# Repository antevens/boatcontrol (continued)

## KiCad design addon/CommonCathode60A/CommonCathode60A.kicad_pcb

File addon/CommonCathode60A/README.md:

Addon board for Boatcontrol 32.

The Boatcontrol 32 is a smart distribution panel and electrical system for on/off-grid and hybrid backup power systems that need to handle 12-24v DC 110-115v AC and 200-250V AC systems.
A perfect companion to a SMA Sunny Island or Sunny Boy Storage, Fronius or other battery inverters.

It's a one stop PCB that allows a Raspberry Pi (RPi) or Nvidia Jetson to control your entire electrical system while retaining full analog control from external switches and allowing manual override onboard in case of emergencies.
This addon board adds 8 x 60 AC/DC relays.
https://github.com/antevens/boatcontrol/tree/master/addon/CommonCathode60A

BoatControl
https://github.com/antevens/boatcontrol

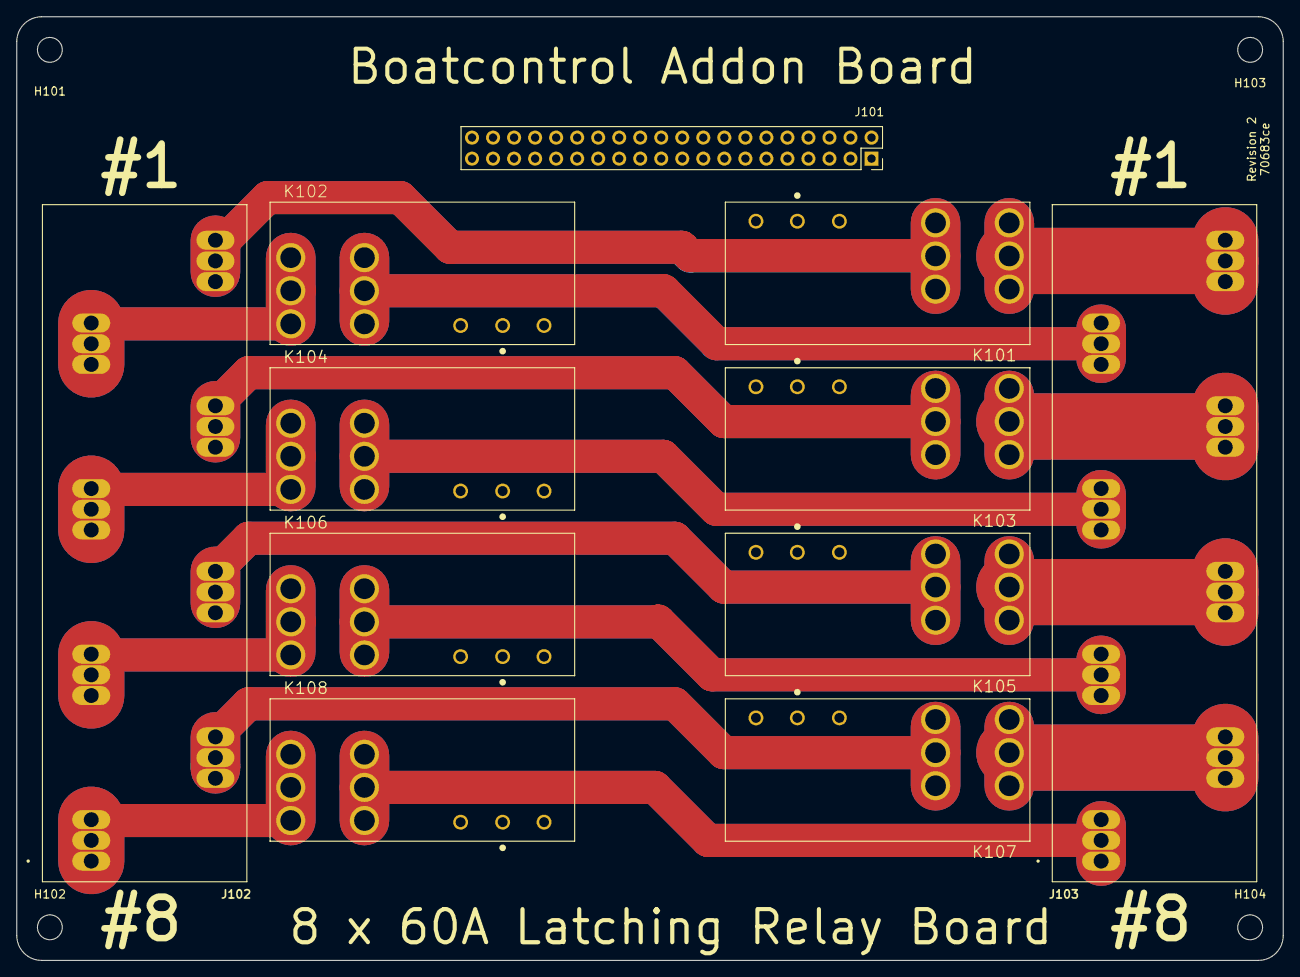
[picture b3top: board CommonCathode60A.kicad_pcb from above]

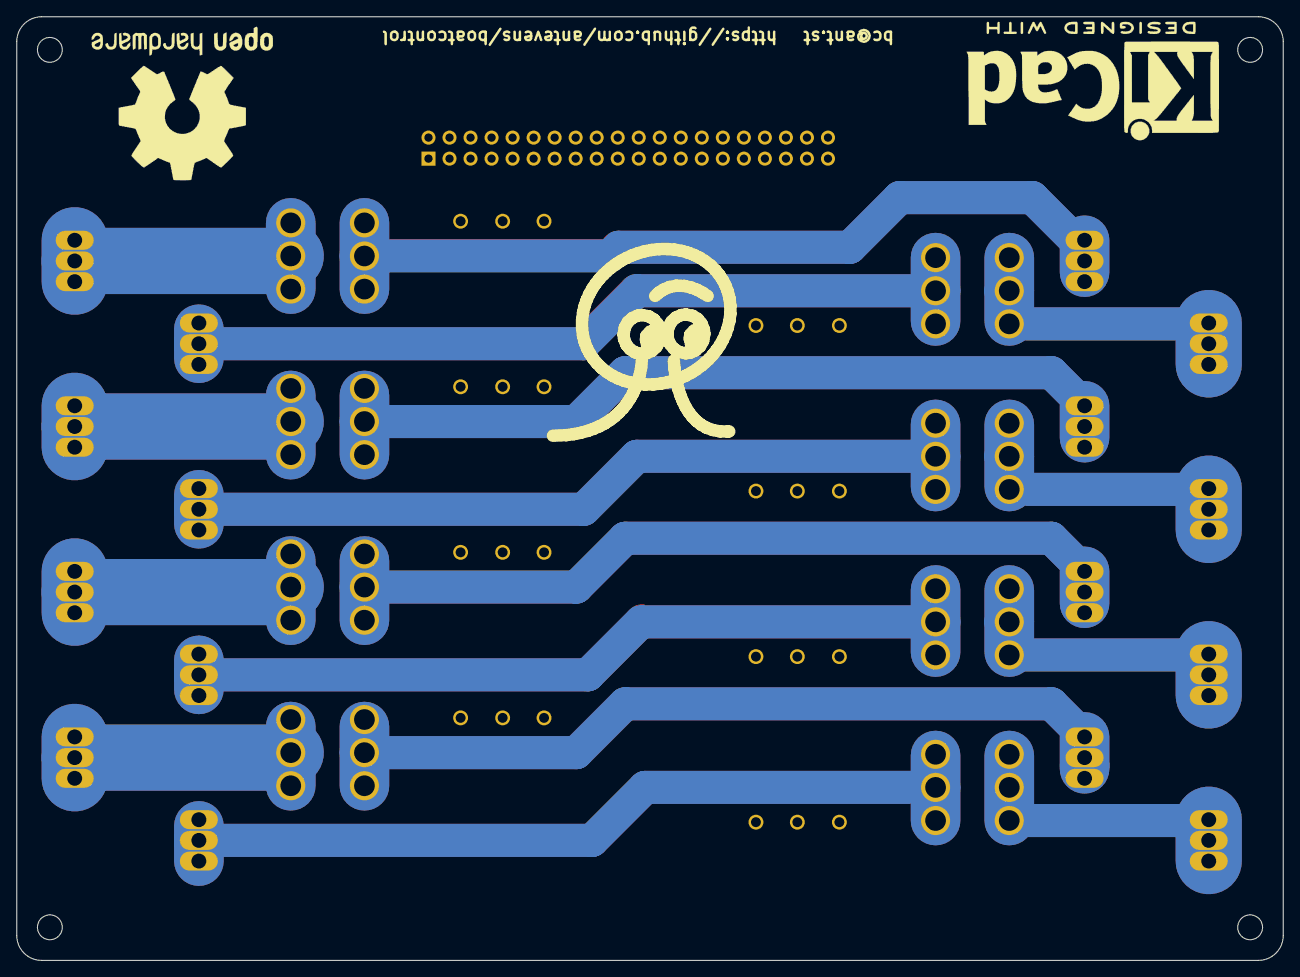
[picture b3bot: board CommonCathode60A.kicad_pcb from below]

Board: 4 copper layers, 153.0 x 114.0 mm, 18 parts (3 on the bottom side), 33 nets.

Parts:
G102: LOGO_ANT; Ant_Logo_SilkScreen
H101, H102, H103, H104: MountingHole; MountingHole_3mm
J101: Conn_02x20_Odd_Even Header; PinSocket_2x20_P2.54mm_Vertical
J102, J103: TBL008V-1000-08BE; CUI_TBL008V-1000-08BE
K101, K102, K103, K104, K105, K106, K107, K108: EW60-1A3-CL12D04; TE_2071366-2
LOGO101: Logo_Open_Hardware_Large; KiCad-Logo2_12mm_SilkScreen
LOGO102: Logo_Open_Hardware_Large; OSHW-Logo2_24.3x20mm_SilkScreen

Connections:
/K1_COIL_OFF: J101.3, J101.4, K101.A2
/K1_COIL_ON: J101.1, J101.2, K101.A3
/K1_IN: J102.8_1, J102.8_2, J102.8_3, K101.4, K101.5, K101.6
/K1_OUT: J103.8_1, J103.8_2, J103.8_3, K101.1, K101.2, K101.3
/K2_COIL_OFF: J101.7, J101.8, K102.A3
/K2_COIL_ON: J101.5, J101.6, K102.A2
/K2_IN: J102.7_1, J102.7_2, J102.7_3, K102.1, K102.2, K102.3
/K2_OUT: J103.7_1, J103.7_2, J103.7_3, K102.4, K102.5, K102.6
/K3_COIL_OFF: J101.11, J101.12, K103.A2
/K3_COIL_ON: J101.9, J101.10, K103.A3
/K3_IN: J102.6_1, J102.6_2, J102.6_3, K103.4, K103.5, K103.6
/K3_OUT: J103.6_1, J103.6_2, J103.6_3, K103.1, K103.2, K103.3
/K4_COIL_OFF: J101.15, J101.16, K104.A3
/K4_COIL_ON: J101.13, J101.14, K104.A2
/K4_IN: J102.5_1, J102.5_2, J102.5_3, K104.1, K104.2, K104.3
/K4_OUT: J103.5_1, J103.5_2, J103.5_3, K104.4, K104.5, K104.6
/K5_COIL_OFF: J101.19, J101.20, K105.A2
/K5_COIL_ON: J101.17, J101.18, K105.A3
/K5_IN: J102.4_1, J102.4_2, J102.4_3, K105.4, K105.5, K105.6
/K5_OUT: J103.4_1, J103.4_2, J103.4_3, K105.1, K105.2, K105.3
/K6_COIL_OFF: J101.23, J101.24, K106.A3
/K6_COIL_ON: J101.21, J101.22, K106.A2
/K6_IN: J102.3_1, J102.3_2, J102.3_3, K106.1, K106.2, K106.3
/K6_OUT: J103.3_1, J103.3_2, J103.3_3, K106.4, K106.5, K106.6
/K7_COIL_OFF: J101.27, J101.28, K107.A2
/K7_COIL_ON: J101.25, J101.26, K107.A3
/K7_IN: J102.2_1, J102.2_2, J102.2_3, K107.4, K107.5, K107.6
/K7_OUT: J103.2_1, J103.2_2, J103.2_3, K107.1, K107.2, K107.3
/K8_COIL_OFF: J101.31, J101.32, K108.A3
/K8_COIL_ON: J101.29, J101.30, K108.A2
/K8_IN: J102.1_1, J102.1_2, J102.1_3, K108.1, K108.2, K108.3
/K8_OUT: J103.1_1, J103.1_2, J103.1_3, K108.4, K108.5, K108.6
GND: J101.33, J101.34, J101.35, J101.36, J101.37, J101.38, J101.39, J101.40, K101.A1, K102.A1, K103.A1, K104.A1, K105.A1, K106.A1, K107.A1, K108.A1

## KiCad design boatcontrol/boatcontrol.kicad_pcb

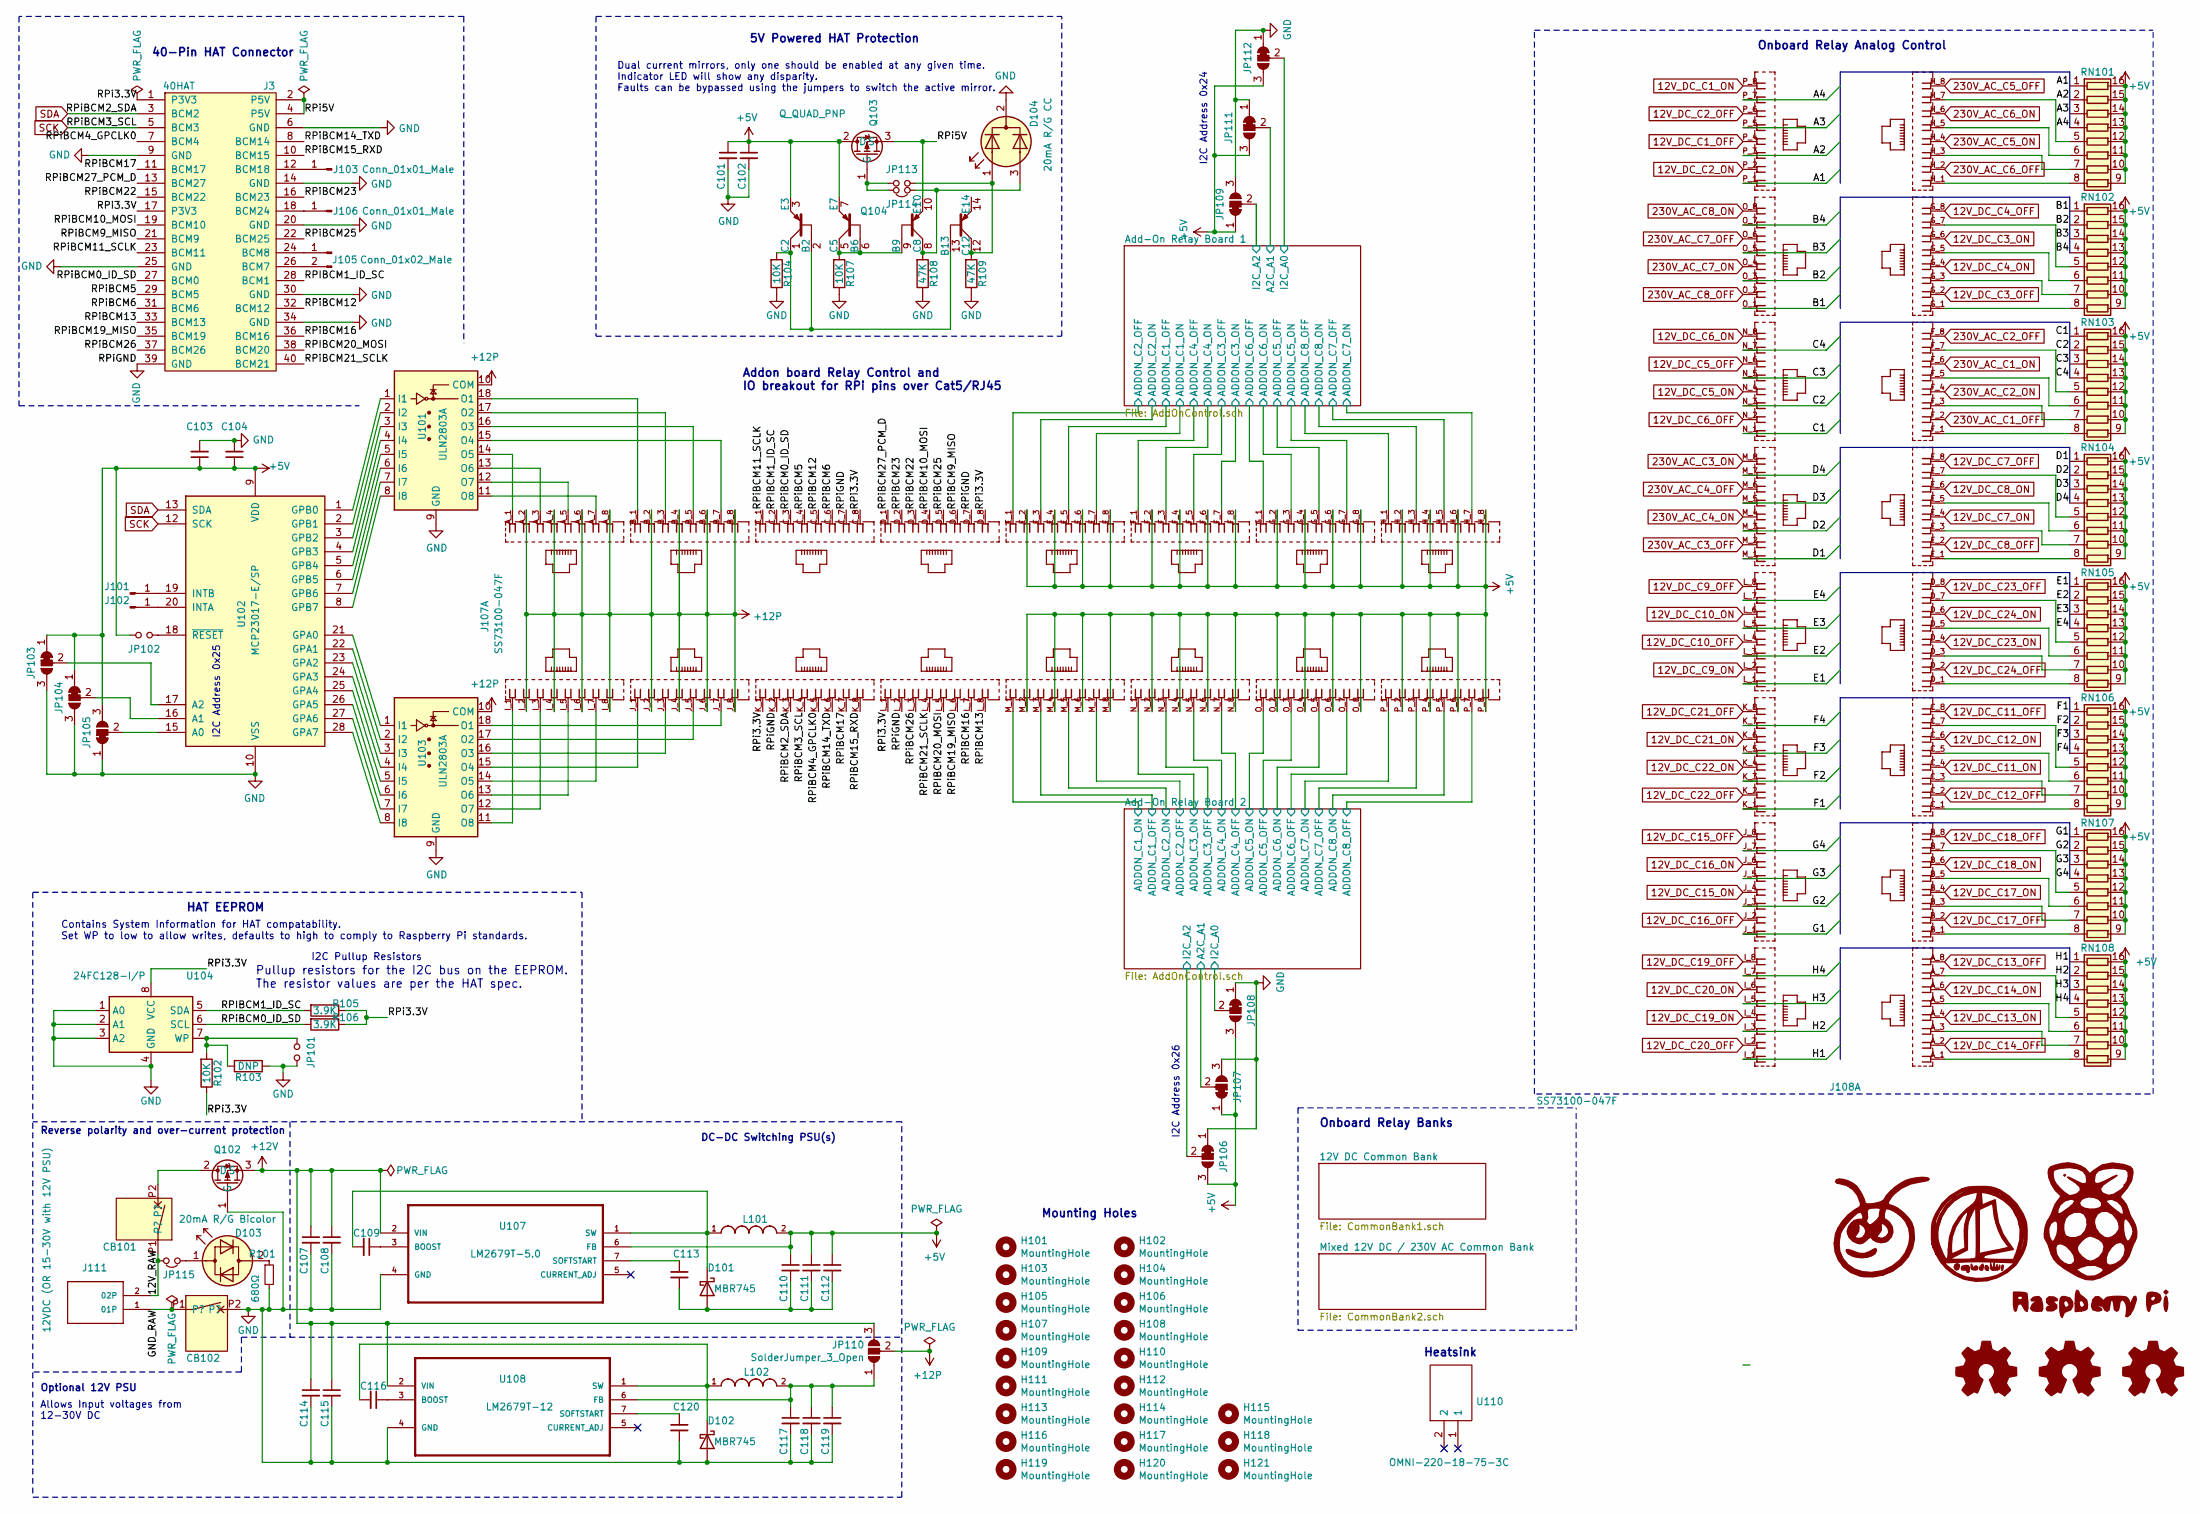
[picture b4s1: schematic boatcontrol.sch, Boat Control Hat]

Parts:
C101, C112, C119: 10uF; CP_Radial_D8.0mm_P5.00mm
C102: 0.1uF; CP_Radial_D8.0mm_P5.00mm
C103: 10uF; C_Disc_D7.5mm_W5.0mm_P5.00mm
C104: 0.1uF; C_Disc_D7.5mm_W5.0mm_P5.00mm
C107, C114: Illinois Capacitor; CP_Radial_D10.0mm_P5.00mm
C108, C111, C115, C118: 0.22uF; CP_Radial_D8.0mm_P5.00mm
C109, C116: C320C103K1R5TA; CP_Radial_D5.0mm_P2.50mm
C110, C117: 330UF; CP_Radial_D10.0mm_P5.00mm
C113: C315C102K1R5TA7301; CP_Radial_D5.0mm_P2.50mm
C120: C315C272K1R5TA; CP_Radial_D5.0mm_P2.50mm
CB101, CB102: SchurterCircuitBreaker 3a; Schurter_Circuit_Breaker
D101, D102: MBR745; TO-220
D103: 20mA R/G Bicolor; LED_D5.0mm
D104: 20mA R/G CC; LED_D5.0mm-3
G101: LOGO_ANT; Ant_Logo_SilkScreen
G102: LOGO_RUGLUDALLUR; Rugludallur-Logo_SilkScreen
G104: LOGO_RPI; RPi_Logo_SilkScreen
H101, H102, H103, H104, H105, H106, H107, H108, H109, H110, H111, H112, H113, H114, H115, H116, H117, H118, H119, H120, H121: MountingHole; MountingHole_3mm
J3: 40HAT; Raspberry_Pi_Any_Socketed_THT_FaceDown_MountingHoles
J101, J102: Conn_01x01_Male; PinHeader_1x01_P2.54mm_Vertical
J103, J106: Conn_01x01_Male; PinHeader_1x01_P2.00mm_Vertical
J105: Conn_01x02_Male; PinHeader_1x02_P2.00mm_Vertical
J107, J108: SS73100-047F; STEWART_SS73100-047F
J111: TBL008V-1000-02BE; CUI_TBP02R2W-381-02BE
JP101, JP102, JP113: Jumper_NO_Small; PinHeader_1x02_P2.54mm_Vertical
JP103, JP104, JP105, JP106, JP107, JP108, JP109, JP111, JP112: SolderJumper_3_Bridged12; SolderJumper-3_P1.3mm_Bridged12_RoundedPad1.0x1.5mm
JP110: SolderJumper_3_Open; SolderJumper-3_P1.3mm_Open_RoundedPad3.0x4.5mm_NumberLabels
JP114, JP115: Jumper_NC_Small; PinHeader_1x02_P2.54mm_Vertical
L101: 15µH; L_Toroid_Horizontal_Vertical_2103-RC_P19.403mm_Bourns_2100
L102: 10µH; L_Toroid_Horizontal_Vertical_2000-100-RC_P14.244mm_Bourns_2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
LOGO101: Open Hardware; OSHW-Logo2_48.7x40mm_SilkScreen
LOGO102: Logo_Open_Hardware_Small; KiCad-Logo2_40mm_SilkScreen
LOGO103: Logo_Open_Hardware_Small; OSHW-Logo_38.1x40mm_SilkScreen
Q102, Q103: IPP120P04P4L-03; TO-220-3_Vertical
Q104: Q_QUAD_PNP; DIP-14_W7.62mm
R101: 680Ω; R_Axial_DIN0207_L6.3mm_D2.5mm_P7.62mm_Horizontal
R102, R104, R107: 10K; R_Axial_DIN0207_L6.3mm_D2.5mm_P7.62mm_Horizontal
R103: DNP; R_Axial_DIN0207_L6.3mm_D2.5mm_P7.62mm_Horizontal
R105, R106: 3.9K; R_Axial_DIN0207_L6.3mm_D2.5mm_P7.62mm_Horizontal
R108, R109: 47K; R_Axial_DIN0207_L6.3mm_D2.5mm_P7.62mm_Horizontal
RN101, RN102, RN103, RN104, RN105, RN106, RN107, RN108: 10KΩ; SOIC-16W_5.3x10.2mm_P1.27mm; Manufacturer_Part_Number 4816P-103LF-ND
U101, U103: ULN2803A; DIP-18_W7.62mm
U102: MCP23017-E/SP; DIP-28_W7.62mm
U104: 24FC128-I/P; DIP-8_W7.62mm
U107: LM2679T-5.0; TO-220-7_P2.54x3.7mm_StaggerOdd_Lead3.8mm_Vertical
U108: LM2679T-12; TO-220-7_P2.54x3.7mm_StaggerOdd_Lead3.8mm_Vertical
U110: OMNI-220-18-75-3C; OMNI22018753C; Manufacturer_Part_Number OMNI-220-18-75-3C; Mouser Part Number 567-OMNI220-18-75-3C

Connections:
12V_DC_C3_OFF: J108.G_2 (2); also elsewhere on the board
12V_DC_C3_ON: J108.G_6 (6); also elsewhere on the board
12V_DC_C4_OFF: J108.G_8 (8); also elsewhere on the board
12V_DC_C4_ON: J108.G_4 (4); also elsewhere on the board
12V_DC_C5_OFF: J108.N_6 (6); also elsewhere on the board
12V_DC_C5_ON: J108.N_4 (4); also elsewhere on the board
12V_DC_C6_OFF: J108.N_2 (2); also elsewhere on the board
12V_DC_C6_ON: J108.N_8 (8); also elsewhere on the board
12V_DC_C7_OFF: J108.E_8 (8); also elsewhere on the board
12V_DC_C7_ON: J108.E_4 (4); also elsewhere on the board
12V_DC_C8_OFF: J108.E_2 (2); also elsewhere on the board
12V_DC_C8_ON: J108.E_6 (6); also elsewhere on the board
12V_DC_C9_OFF: J108.L_8 (8); also elsewhere on the board
12V_DC_C9_ON: J108.L_2 (2); also elsewhere on the board
12V_DC_C10_OFF: J108.L_4 (4); also elsewhere on the board
12V_DC_C10_ON: J108.L_6 (6); also elsewhere on the board
12V_DC_C13_OFF: J108.A_8 (8); also elsewhere on the board
12V_DC_C13_ON: J108.A_4 (4); also elsewhere on the board
12V_DC_C14_OFF: J108.A_2 (2); also elsewhere on the board
12V_DC_C14_ON: J108.A_6 (6); also elsewhere on the board
12V_DC_C15_OFF: J108.J_8 (8); also elsewhere on the board
12V_DC_C15_ON: J108.J_4 (4); also elsewhere on the board
12V_DC_C16_OFF: J108.J_2 (2); also elsewhere on the board
12V_DC_C16_ON: J108.J_6 (6); also elsewhere on the board
12V_DC_C17_OFF: J108.B_2 (2); also elsewhere on the board
12V_DC_C17_ON: J108.B_4 (4); also elsewhere on the board
12V_DC_C18_OFF: J108.B_8 (8); also elsewhere on the board
12V_DC_C18_ON: J108.B_6 (6); also elsewhere on the board
12V_DC_C19_OFF: J108.I_8 (8); also elsewhere on the board
12V_DC_C19_ON: J108.I_4 (4); also elsewhere on the board
12V_DC_C20_OFF: J108.I_2 (2); also elsewhere on the board
12V_DC_C20_ON: J108.I_6 (6); also elsewhere on the board
12V_DC_C21_OFF: J108.K_8 (8); also elsewhere on the board
12V_DC_C21_ON: J108.K_6 (6); also elsewhere on the board
12V_DC_C22_OFF: J108.K_2 (2); also elsewhere on the board
12V_DC_C22_ON: J108.K_4 (4); also elsewhere on the board
12V_DC_C23_OFF: J108.D_8 (8); also elsewhere on the board
12V_DC_C23_ON: J108.D_4 (4); also elsewhere on the board
12V_DC_C24_OFF: J108.D_2 (2); also elsewhere on the board
12V_DC_C24_ON: J108.D_6 (6); also elsewhere on the board
230V_AC_C1_OFF: J108.F_2 (2); also elsewhere on the board
230V_AC_C1_ON: J108.F_6 (6); also elsewhere on the board
230V_AC_C2_OFF: J108.F_8 (8); also elsewhere on the board
230V_AC_C2_ON: J108.F_4 (4); also elsewhere on the board
230V_AC_C3_OFF: J108.M_2 (2); also elsewhere on the board
230V_AC_C3_ON: J108.M_8 (8); also elsewhere on the board
230V_AC_C4_OFF: J108.M_6 (6); also elsewhere on the board
230V_AC_C4_ON: J108.M_4 (4); also elsewhere on the board
230V_AC_C5_OFF: J108.H_8 (8); also elsewhere on the board
230V_AC_C5_ON: J108.H_4 (4); also elsewhere on the board
230V_AC_C6_OFF: J108.H_2 (2); also elsewhere on the board
230V_AC_C6_ON: J108.H_6 (6); also elsewhere on the board
230V_AC_C7_OFF: J108.O_6 (6); also elsewhere on the board
230V_AC_C7_ON: J108.O_4 (4); also elsewhere on the board
230V_AC_C8_OFF: J108.O_2 (2); also elsewhere on the board
230V_AC_C8_ON: J108.O_8 (8); also elsewhere on the board
+5V: C101.1, C102.1, C103.1, C104.1, C110.1, C111.1, C112.1, J107.E_2 (2), J107.E_4 (4), J107.E_6 (6), J107.E_8 (8), J107.F_2 (2), J107.F_4 (4), J107.F_6 (6), J107.F_8 (8), J107.G_2 (2), J107.G_4 (4), J107.G_6 (6), J107.G_8 (8), J107.H_2 (2), J107.H_4 (4), J107.H_6 (6), J107.H_8 (8), J107.M_2 (2), J107.M_4 (4), J107.M_6 (6), J107.M_8 (8), J107.N_2 (2), J107.N_4 (4), J107.N_6 (6), J107.N_8 (8), J107.O_2 (2), J107.O_4 (4), J107.O_6 (6), J107.O_8 (8), J107.P_2 (2), J107.P_4 (4), J107.P_6 (6), J107.P_8 (8), JP102.2, JP103.1 (A), JP104.1 (A), JP105.3 (B), JP106.3 (B), JP107.1 (A), JP108.3 (B), JP109.1 (A), JP111.3 (B), JP112.3 (B), L101.2, Q103.2 (D), Q104.3 (E3), Q104.7 (E7), RN101.9 (R8.2), RN101.10 (R7.2), RN101.11 (R6.2), RN101.12 (R5.2), RN101.13 (R4.2), RN101.14 (R3.2), RN101.15 (R2.2), RN101.16 (R1.2), RN102.9 (R8.2), RN102.10 (R7.2), RN102.11 (R6.2), RN102.12 (R5.2), RN102.13 (R4.2), RN102.14 (R3.2), RN102.15 (R2.2), RN102.16 (R1.2), RN103.9 (R8.2), RN103.10 (R7.2), RN103.11 (R6.2), RN103.12 (R5.2), RN103.13 (R4.2), RN103.14 (R3.2), RN103.15 (R2.2), RN103.16 (R1.2), RN104.9 (R8.2), RN104.10 (R7.2), RN104.11 (R6.2), RN104.12 (R5.2), RN104.13 (R4.2), RN104.14 (R3.2), RN104.15 (R2.2), RN104.16 (R1.2), RN105.9 (R8.2), RN105.10 (R7.2), RN105.11 (R6.2), RN105.12 (R5.2), RN105.13 (R4.2), RN105.14 (R3.2), RN105.15 (R2.2), RN105.16 (R1.2), RN106.9 (R8.2), RN106.10 (R7.2), RN106.11 (R6.2), RN106.12 (R5.2), RN106.13 (R4.2), RN106.14 (R3.2), RN106.15 (R2.2), RN106.16 (R1.2), RN107.9 (R8.2), RN107.10 (R7.2), RN107.11 (R6.2), RN107.12 (R5.2), RN107.13 (R4.2), RN107.14 (R3.2), RN107.15 (R2.2), RN107.16 (R1.2), RN108.9 (R8.2), RN108.10 (R7.2), RN108.11 (R6.2), RN108.12 (R5.2), RN108.13 (R4.2), RN108.14 (R3.2), RN108.15 (R2.2), RN108.16 (R1.2), U102.9 (VDD), U107.6 (FB); also elsewhere on the board
+12P: J107.A_2 (2), J107.A_4 (4), J107.A_6 (6), J107.A_8 (8), J107.B_2 (2), J107.B_4 (4), J107.B_6 (6), J107.B_8 (8), J107.I_2 (2), J107.I_4 (4), J107.I_6 (6), J107.I_8 (8), J107.J_2 (2), J107.J_4 (4), J107.J_6 (6), J107.J_8 (8), JP110.2 (C), U101.10 (COM), U103.10 (COM); also elsewhere on the board
+12V: C107.1, C108.1, C114.1, C115.1, JP110.3 (B), Q102.3 (S), U107.2 (VIN), U108.2 (VIN)
/12V_RAW: CB101.P1, J111.2 (02P), JP115.2
/A1: J108.P_1 (1), RN101.1 (R1.1)
/A2: J108.P_3 (3), RN101.2 (R2.1)
/A3: J108.P_5 (5), RN101.3 (R3.1)
/A4: J108.P_7 (7), RN101.4 (R4.1)
/Add-On Relay Board 1/A2C_A1: JP111.2 (C); also elsewhere on the board
/Add-On Relay Board 1/ADDON_C1_OFF: J107.E_5 (5); also elsewhere on the board
/Add-On Relay Board 1/ADDON_C1_ON: J107.E_7 (7); also elsewhere on the board
/Add-On Relay Board 1/ADDON_C2_OFF: J107.E_1 (1); also elsewhere on the board
/Add-On Relay Board 1/ADDON_C2_ON: J107.E_3 (3); also elsewhere on the board
/Add-On Relay Board 1/ADDON_C3_OFF: J107.F_5 (5); also elsewhere on the board
/Add-On Relay Board 1/ADDON_C3_ON: J107.F_7 (7); also elsewhere on the board
/Add-On Relay Board 1/ADDON_C4_OFF: J107.F_1 (1); also elsewhere on the board
/Add-On Relay Board 1/ADDON_C4_ON: J107.F_3 (3); also elsewhere on the board
/Add-On Relay Board 1/ADDON_C5_OFF: J107.G_5 (5); also elsewhere on the board
/Add-On Relay Board 1/ADDON_C5_ON: J107.G_7 (7); also elsewhere on the board
/Add-On Relay Board 1/ADDON_C6_OFF: J107.G_1 (1); also elsewhere on the board
/Add-On Relay Board 1/ADDON_C6_ON: J107.G_3 (3); also elsewhere on the board
/Add-On Relay Board 1/ADDON_C7_OFF: J107.H_5 (5); also elsewhere on the board
/Add-On Relay Board 1/ADDON_C7_ON: J107.H_7 (7); also elsewhere on the board
/Add-On Relay Board 1/ADDON_C8_OFF: J107.H_1 (1); also elsewhere on the board
/Add-On Relay Board 1/ADDON_C8_ON: J107.H_3 (3); also elsewhere on the board
/Add-On Relay Board 1/I2C_A0: JP112.2 (C); also elsewhere on the board
/Add-On Relay Board 1/I2C_A2: JP109.2 (C); also elsewhere on the board
/Add-On Relay Board 2/A2C_A1: JP107.2 (C); also elsewhere on the board
/Add-On Relay Board 2/ADDON_C1_OFF: J107.M_3 (3); also elsewhere on the board
/Add-On Relay Board 2/ADDON_C1_ON: J107.M_1 (1); also elsewhere on the board
/Add-On Relay Board 2/ADDON_C2_OFF: J107.M_7 (7); also elsewhere on the board
/Add-On Relay Board 2/ADDON_C2_ON: J107.M_5 (5); also elsewhere on the board
/Add-On Relay Board 2/ADDON_C3_OFF: J107.N_3 (3); also elsewhere on the board
/Add-On Relay Board 2/ADDON_C3_ON: J107.N_1 (1); also elsewhere on the board
/Add-On Relay Board 2/ADDON_C4_OFF: J107.N_7 (7); also elsewhere on the board
/Add-On Relay Board 2/ADDON_C4_ON: J107.N_5 (5); also elsewhere on the board
/Add-On Relay Board 2/ADDON_C5_OFF: J107.O_3 (3); also elsewhere on the board
/Add-On Relay Board 2/ADDON_C5_ON: J107.O_1 (1); also elsewhere on the board
/Add-On Relay Board 2/ADDON_C6_OFF: J107.O_7 (7); also elsewhere on the board
/Add-On Relay Board 2/ADDON_C6_ON: J107.O_5 (5); also elsewhere on the board
/Add-On Relay Board 2/ADDON_C7_OFF: J107.P_3 (3); also elsewhere on the board
/Add-On Relay Board 2/ADDON_C7_ON: J107.P_1 (1); also elsewhere on the board
/Add-On Relay Board 2/ADDON_C8_OFF: J107.P_7 (7); also elsewhere on the board
/Add-On Relay Board 2/ADDON_C8_ON: J107.P_5 (5); also elsewhere on the board
/Add-On Relay Board 2/I2C_A0: JP108.2 (C); also elsewhere on the board
/Add-On Relay Board 2/I2C_A2: JP106.2 (C); also elsewhere on the board
/B1: J108.O_1 (1), RN102.1 (R1.1)
/B2: J108.O_3 (3), RN102.2 (R2.1)
/B3: J108.O_5 (5), RN102.3 (R3.1)
/B4: J108.O_7 (7), RN102.4 (R4.1)
/C1: J108.N_1 (1), RN103.1 (R1.1)
/C2: J108.N_3 (3), RN103.2 (R2.1)
/C3: J108.N_5 (5), RN103.3 (R3.1)
/C4: J108.N_7 (7), RN103.4 (R4.1)
/D1: J108.M_1 (1), RN104.1 (R1.1)
/D2: J108.M_3 (3), RN104.2 (R2.1)
/D3: J108.M_5 (5), RN104.3 (R3.1)
/D4: J108.M_7 (7), RN104.4 (R4.1)
/E1: J108.L_1 (1), RN105.1 (R1.1)
/E2: J108.L_3 (3), RN105.2 (R2.1)
/E3: J108.L_5 (5), RN105.3 (R3.1)
/E4: J108.L_7 (7), RN105.4 (R4.1)
/F1: J108.K_1 (1), RN106.1 (R1.1)
/F2: J108.K_3 (3), RN106.2 (R2.1)
/F3: J108.K_5 (5), RN106.3 (R3.1)
/F4: J108.K_7 (7), RN106.4 (R4.1)
/G1: J108.J_1 (1), RN107.1 (R1.1)
/G2: J108.J_3 (3), RN107.2 (R2.1)
/G3: J108.J_5 (5), RN107.3 (R3.1)
/G4: J108.J_7 (7), RN107.4 (R4.1)
/GND_RAW: CB102.P1, J111.1 (01P)
/H1: J108.I_1 (1), RN108.1 (R1.1)
/H2: J108.I_3 (3), RN108.2 (R2.1)
/H3: J108.I_5 (5), RN108.3 (R3.1)
/H4: J108.I_7 (7), RN108.4 (R4.1)
/RPIBCM1_ID_SC: J3.28 (BCM1), J107.C_2 (2), R105.2, U104.5 (SDA)
/RPIBCM20_MOSI: J3.38 (BCM20), J107.L_5 (5)
/RPi3.3V: J3.1 (P3V3), J3.17 (P3V3), J107.C_8 (8), J107.D_8 (8), J107.K_1 (1), J107.L_1 (1), R102.1, R105.1, R106.1, U104.8 (VCC)
/RPi5V: J3.2 (P5V), J3.4 (P5V), Q103.3 (S), Q104.10 (E10)
/RPiBCM0_ID_SD: J3.27 (BCM0), J107.C_3 (3), R106.2, U104.6 (SCL)
/RPiBCM4_GPCLK0: J3.7 (BCM4), J107.K_5 (5)
/RPiBCM5: J3.29 (BCM5), J107.C_4 (4)
/RPiBCM6: J3.31 (BCM6), J107.C_6 (6)
/RPiBCM9_MISO: J3.21 (BCM9), J107.D_6 (6)
/RPiBCM10_MOSI: J3.19 (BCM10), J107.D_4 (4)
/RPiBCM11_SCLK: J3.23 (BCM11), J107.C_1 (1)
/RPiBCM12: J3.32 (BCM12), J107.C_5 (5)
/RPiBCM13: J3.33 (BCM13), J107.L_8 (8)
/RPiBCM14_TXD: J3.8 (BCM14), J107.K_6 (6)
/RPiBCM15_RXD: J3.10 (BCM15), J107.K_8 (8)
/RPiBCM16: J3.36 (BCM16), J107.L_7 (7)
/RPiBCM17: J3.11 (BCM17), J107.K_7 (7)
/RPiBCM19_MISO: J3.35 (BCM19), J107.L_6 (6)
/RPiBCM21_SCLK: J3.40 (BCM21), J107.L_4 (4)
/RPiBCM22: J3.15 (BCM22), J107.D_3 (3)
/RPiBCM23: J3.16 (BCM23), J107.D_2 (2)
/RPiBCM25: J3.22 (BCM25), J107.D_5 (5)
/RPiBCM26: J3.37 (BCM26), J107.L_3 (3)
/RPiBCM27_PCM_D: J3.13 (BCM27), J107.D_1 (1)
GND: C101.2, C102.2, C103.2, C104.2, C107.2, C108.2, C114.2, C115.2, C117.2, C118.2, C119.2, C120.2, CB102.P2, D102.2 (A), D104.2 (K), J3.6 (GND), J3.9 (GND), J3.14 (GND), J3.20 (GND), J3.25 (GND), J3.30 (GND), J3.34 (GND), J3.39 (GND), J107.C_7 (7), J107.D_7 (7), J107.K_2 (2), J107.L_2 (2), JP101.2, JP103.3 (B), JP104.3 (B), JP105.1 (A), JP106.1 (A), JP107.3 (B), JP108.1 (A), JP109.3 (B), JP111.1 (A), JP112.1 (A), Q102.1 (G), R101.2, R103.2, R104.1, R107.1, R108.1, R109.1, U101.9 (GND), U102.10 (VSS), U103.9 (GND), U104.1 (A0), U104.2 (A1), U104.3 (A2), U104.4 (GND), U107.4 (GND), U108.4 (GND); also elsewhere on the board
unnamed: C109.1, U107.3 (BOOST)
unnamed: C109.2, D101.1 (K), L101.1, U107.1 (SW)
unnamed: C110.2, C111.2, C112.2, C113.2, D101.2 (A)
unnamed: C113.1, U107.7 (SOFTSTART)
unnamed: C116.1, U108.3 (BOOST)
unnamed: C116.2, D102.1 (K), L102.1, U108.1 (SW)
unnamed: C117.1, C118.1, C119.1, JP110.1 (A), L102.2, U108.6 (FB)
unnamed: C120.1, U108.7 (SOFTSTART)
unnamed: CB101.P2, Q102.2 (D)
unnamed: D103.1 (KA), JP115.1
unnamed: D103.2 (AK), R101.1
unnamed: D104.1 (A1), JP113.2, Q104.12 (C12), R109.2
unnamed: D104.3 (A2), JP114.1, Q104.8 (C8), R108.2
unnamed: J101.1, U102.19 (INTB)
unnamed: J102.1, U102.20 (INTA)
unnamed: J3.12 (BCM18), J103.1
unnamed: J3.24 (BCM8), J105.1
unnamed: J3.26 (BCM7), J105.2
unnamed: J3.18 (BCM24), J106.1
unnamed: J107.A_1 (1), U101.14 (O5)
unnamed: J107.A_3 (3), U101.13 (O6)
unnamed: J107.A_5 (5), U101.12 (O7)
unnamed: J107.A_7 (7), U101.11 (O8)
unnamed: J107.B_1 (1), U101.18 (O1)
unnamed: J107.B_3 (3), U101.17 (O2)
unnamed: J107.B_5 (5), U101.16 (O3)
unnamed: J107.B_7 (7), U101.15 (O4)
unnamed: J107.I_1 (1), U103.11 (O8)
unnamed: J107.I_3 (3), U103.12 (O7)
unnamed: J107.I_5 (5), U103.13 (O6)
unnamed: J107.I_7 (7), U103.14 (O5)
unnamed: J107.J_1 (1), U103.15 (O4)
unnamed: J107.J_3 (3), U103.16 (O3)
unnamed: J107.J_5 (5), U103.17 (O2)
unnamed: J107.J_7 (7), U103.18 (O1)
unnamed: J108.A_1 (1), RN108.8 (R8.1)
unnamed: J108.A_3 (3), RN108.7 (R7.1)
unnamed: J108.A_5 (5), RN108.6 (R6.1)
unnamed: J108.A_7 (7), RN108.5 (R5.1)
unnamed: J108.B_1 (1), RN107.8 (R8.1)
unnamed: J108.B_3 (3), RN107.7 (R7.1)
unnamed: J108.B_5 (5), RN107.6 (R6.1)
unnamed: J108.B_7 (7), RN107.5 (R5.1)
unnamed: J108.C_1 (1), RN106.8 (R8.1)
unnamed: J108.C_3 (3), RN106.7 (R7.1)
unnamed: J108.C_5 (5), RN106.6 (R6.1)
unnamed: J108.C_7 (7), RN106.5 (R5.1)
unnamed: J108.D_1 (1), RN105.8 (R8.1)
unnamed: J108.D_3 (3), RN105.7 (R7.1)
unnamed: J108.D_5 (5), RN105.6 (R6.1)
unnamed: J108.D_7 (7), RN105.5 (R5.1)
unnamed: J108.E_1 (1), RN104.8 (R8.1)
unnamed: J108.E_3 (3), RN104.7 (R7.1)
unnamed: J108.E_5 (5), RN104.6 (R6.1)
unnamed: J108.E_7 (7), RN104.5 (R5.1)
unnamed: J108.F_1 (1), RN103.8 (R8.1)
unnamed: J108.F_3 (3), RN103.7 (R7.1)
unnamed: J108.F_5 (5), RN103.6 (R6.1)
unnamed: J108.F_7 (7), RN103.5 (R5.1)
unnamed: J108.G_1 (1), RN102.8 (R8.1)
unnamed: J108.G_3 (3), RN102.7 (R7.1)
unnamed: J108.G_5 (5), RN102.6 (R6.1)
unnamed: J108.G_7 (7), RN102.5 (R5.1)
unnamed: J108.H_1 (1), RN101.8 (R8.1)
unnamed: J108.H_3 (3), RN101.7 (R7.1)
unnamed: J108.H_5 (5), RN101.6 (R6.1)
unnamed: J108.H_7 (7), RN101.5 (R5.1)
unnamed: JP101.1, R102.2, R103.1, U104.7 (WP)
unnamed: JP102.1, U102.18 (~RESET~)
unnamed: JP103.2 (C), U102.17 (A2)
unnamed: JP104.2 (C), U102.16 (A1)
unnamed: JP105.2 (C), U102.15 (A0)
unnamed: JP113.1, JP114.2, Q103.1 (G)
unnamed: Q104.1 (C2), Q104.2 (B2), Q104.13 (B13), R104.2
unnamed: Q104.5 (C5), Q104.6 (B6), Q104.9 (B9), R107.2
unnamed: U101.1 (I1), U102.1 (GPB0)
unnamed: U101.2 (I2), U102.2 (GPB1)
unnamed: U101.3 (I3), U102.3 (GPB2)
unnamed: U101.4 (I4), U102.4 (GPB3)
unnamed: U101.5 (I5), U102.5 (GPB4)
unnamed: U101.6 (I6), U102.6 (GPB5)
unnamed: U101.7 (I7), U102.7 (GPB6)
unnamed: U101.8 (I8), U102.8 (GPB7)
unnamed: U102.21 (GPA0), U103.1 (I1)
unnamed: U102.22 (GPA1), U103.2 (I2)
unnamed: U102.23 (GPA2), U103.3 (I3)
unnamed: U102.24 (GPA3), U103.4 (I4)
unnamed: U102.25 (GPA4), U103.5 (I5)
unnamed: U102.26 (GPA5), U103.6 (I6)
unnamed: U102.27 (GPA6), U103.7 (I7)
unnamed: U102.28 (GPA7), U103.8 (I8)
SCK: J3.5 (BCM3), J107.K_4 (4), U102.12 (SCK); also elsewhere on the board
SDA: J3.3 (BCM2), J107.K_3 (3), U102.13 (SDA); also elsewhere on the board

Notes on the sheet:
DC-DC Switching PSU(s)
Reverse polarity and over-current protection
Onboard Relay Banks
Allows Input voltages from 12-30V DC
Optional 12V PSU
Mounting Holes
Contains System Information for HAT compatability. Set WP to low to allow writes, defaults to high to comply to Raspberry Pi standards.
HAT EEPROM
I2C Pullup Resistors
Pullup resistors for the I2C bus on the EEPROM. The resistor values are per the HAT spec.
Dual current mirrors, only one should be enabled at any given time. Indicator LED will show any disparity. Faults can be bypassed using the jumpers to switch the active mirror.
5V Powered HAT Protection
40-Pin HAT Connector
I2C Address 0x25
I2C Address 0x26
Addon board Relay Control and IO breakout for RPi pins over Cat5/RJ45
I2C Address 0x24
Heatsink
Onboard Relay Analog Control
